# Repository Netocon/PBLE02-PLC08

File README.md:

# PBLE02-PLC08
Repositório da placa 8 (2026.1) da matéria PBLE02 da Universidade Federal de Itajubá.

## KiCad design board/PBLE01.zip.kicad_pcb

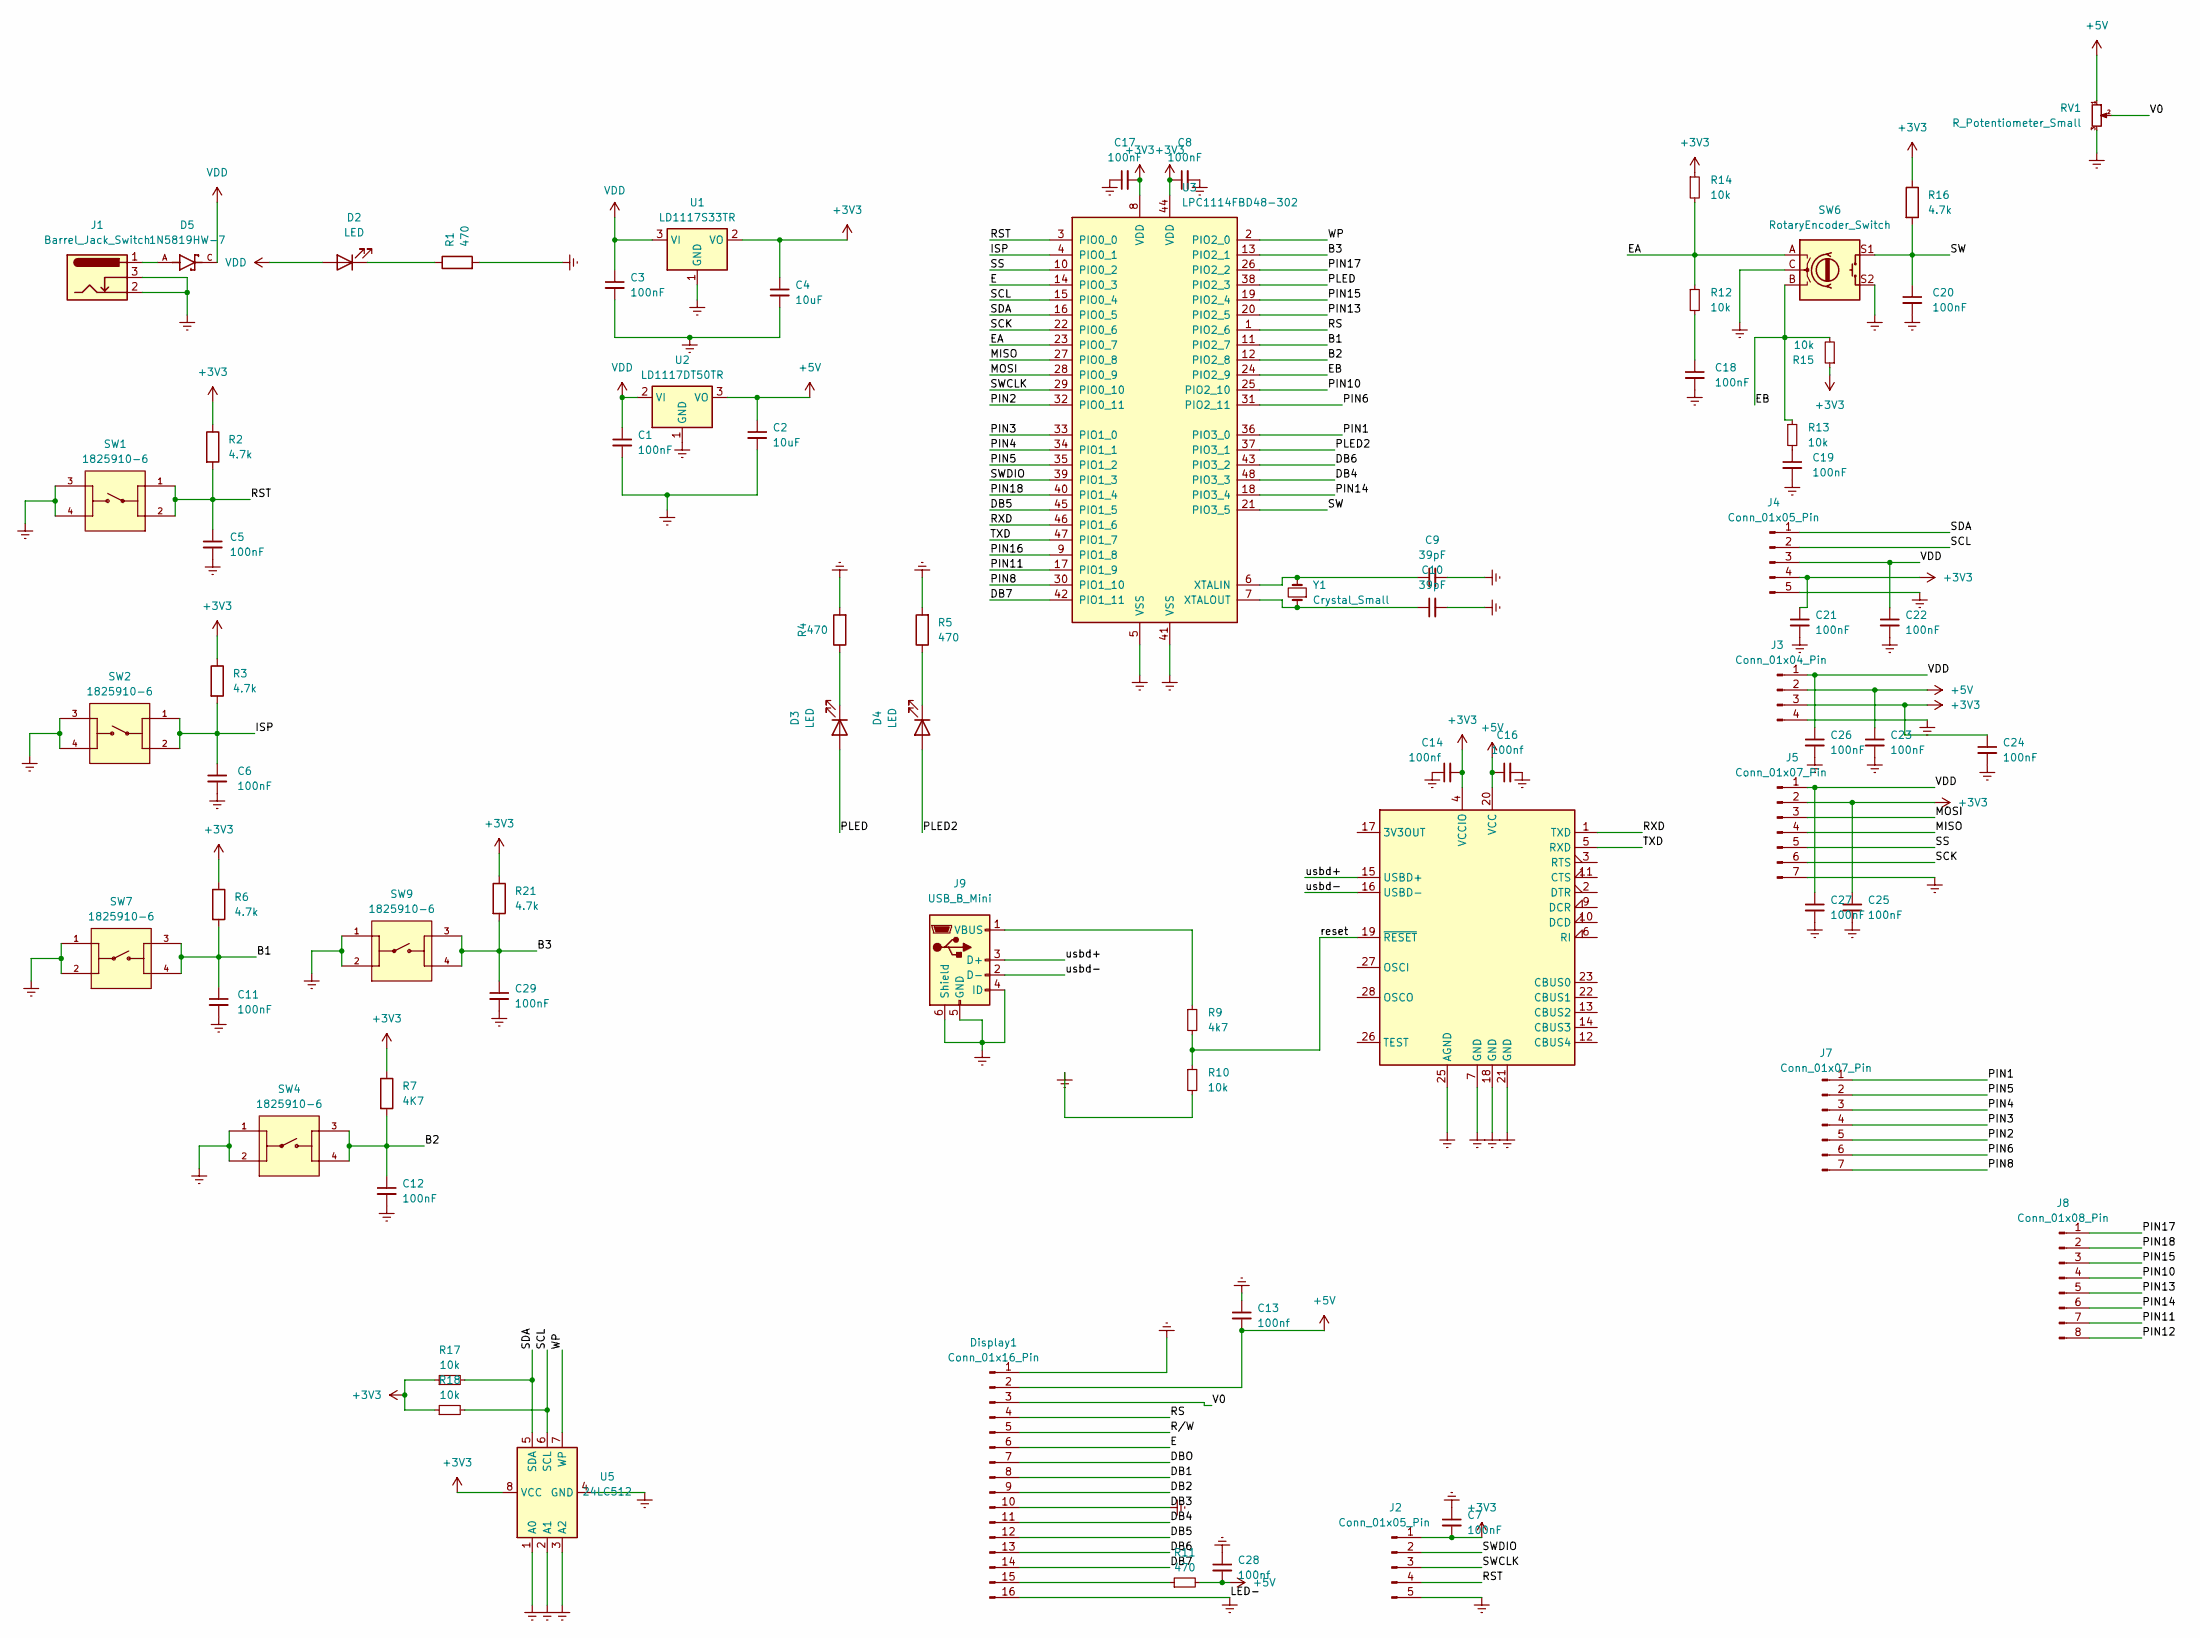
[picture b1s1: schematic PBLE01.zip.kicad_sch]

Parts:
C1, C3, C5, C6, C7, C8, C11, C12, C17, C18, C19, C20, C21, C22, C23, C24, C25, C26, C27, C29: 100nF; C_0805_2012Metric
C2, C4: 10uF; C_0805_2012Metric
C9, C10: 39pF; C_0805_2012Metric
C13, C14, C16, C28: 100nf; C_0805_2012Metric
D2, D3, D4: LED; D_1206_3216Metric
D5: 1N5819HW-7; Diode-1N5819HW7; PARTREV 18-2
Display1: Conn_01x16_Pin; PinHeader_1x16_P2.54mm_Vertical
J1: Barrel_Jack_Switch; CUI_PJ-002A
J2, J4: Conn_01x05_Pin; PinHeader_1x05_P2.54mm_Vertical
J3: Conn_01x04_Pin; PinHeader_1x04_P2.54mm_Vertical
J5, J7: Conn_01x07_Pin; PinHeader_1x07_P2.54mm_Vertical
J8: Conn_01x08_Pin; PinHeader_1x08_P2.54mm_Vertical
J9: USB_B_Mini; USB_Mini-B_Lumberg_2486_01_Horizontal
R1, R4, R5, R11: 470; R_0805_2012Metric
R2, R3, R6, R16, R21: 4.7k; R_0805_2012Metric
R7: 4K7; R_0805_2012Metric
R9: 4k7; R_0805_2012Metric
R10, R12, R13, R14, R15, R17, R18: 10k; R_0805_2012Metric
RV1: R_Potentiometer_Small; Potentiometer_Bourns_3314G_Vertical
SW1, SW2, SW4, SW7, SW9: 1825910-6; SW_1825910-6-4; PARTREV C10
SW6: RotaryEncoder_Switch; RotaryEncoder_Bourns_Vertical_PEC12R-3xxxF-Sxxxx
U1: LD1117S33TR; SOT-223-3_TabPin2
U2: LD1117DT50TR; DPAKSTM
U3: LPC1114FBD48-302; LQFP-48_7x7mm_P0.5mm
U4: FT232RL; SSOP-28_5.3x10.2mm_P0.65mm
U5: 24LC512; E2PROM SOIC127P794X203 8N
Y1: Crystal_Small; Crystal_HC49-4H_Vertical

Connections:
+3V3: C4.1, C7.2, C8.1, C14.2, C17.2, C21.1, C24.1, C25.1, J2.1, J3.3, J4.4, J5.2, R2.1, R3.1, R6.1, R7.1, R14.1, R15.1, R16.1, R17.1, R18.1, R21.1, U1.2 (VO), U3.8 (VDD), U3.44 (VDD), U4.4 (VCCIO), U5.8 (VCC)
+5V: C2.1, C13.2, C16.1, C23.1, C28.2, Display1.2, J3.2, R11.2, RV1.1, U2.3 (VO), U4.20 (VCC); also elsewhere on the board
/B1: C11.1, R6.2, SW7.3, SW7.4, U3.11 (PIO2_7)
/B2: C12.1, R7.2, SW4.3, SW4.4, U3.12 (PIO2_8)
/B3: C29.1, R21.2, SW9.3, SW9.4, U3.13 (PIO2_1)
/DB1: Display1.8
/DB2: Display1.9
/DB4: Display1.11, U3.48 (PIO3_3)
/DB5: Display1.12, U3.45 (PIO1_5)
/DB6: Display1.13, U3.43 (PIO3_2)
/DB7: Display1.14, U3.42 (PIO1_11)
/DBO: Display1.7
/E: Display1.6, U3.14 (PIO0_3)
/EA: R12.1, R14.2, SW6.A, U3.23 (PIO0_7)
/EB: R13.1, R15.2, SW6.B, U3.24 (PIO2_9)
/ISP: C6.1, R3.2, SW2.1, SW2.2, U3.4 (PIO0_1)
/MISO: J5.4, U3.27 (PIO0_8)
/MOSI: J5.3, U3.28 (PIO0_9)
/PIN1: J7.1, U3.36 (PIO3_0)
/PIN2: J7.5, U3.32 (PIO0_11)
/PIN3: J7.4, U3.33 (PIO1_0)
/PIN4: J7.3, U3.34 (PIO1_1)
/PIN5: J7.2, U3.35 (PIO1_2)
/PIN6: J7.6, U3.31 (PIO2_11)
/PIN8: J7.7, U3.30 (PIO1_10)
/PIN10: J8.4, U3.25 (PIO2_10)
/PIN11: J8.7, U3.17 (PIO1_9)
/PIN12: J8.8
/PIN13: J8.5, U3.20 (PIO2_5)
/PIN14: J8.6, U3.18 (PIO3_4)
/PIN15: J8.3, U3.19 (PIO2_4)
/PIN16: U3.9 (PIO1_8)
/PIN17: J8.1, U3.26 (PIO2_2)
/PIN18: J8.2, U3.40 (PIO1_4)
/PLED: D3.2 (A), U3.38 (PIO2_3)
/PLED2: D4.2 (A), U3.37 (PIO3_1)
/RS: Display1.4, U3.1 (PIO2_6)
/RST: C5.1, J2.4, R2.2, SW1.1, SW1.2, U3.3 (PIO0_0)
/RXD: U3.46 (PIO1_6), U4.1 (TXD)
/R/W: Display1.5
/SCK: J5.6, U3.22 (PIO0_6)
/SCL: J4.2, R18.2, U3.15 (PIO0_4), U5.6 (SCL)
/SDA: J4.1, R17.2, U3.16 (PIO0_5), U5.5 (SDA)
/SS: J5.5, U3.10 (PIO0_2)
/SW: C20.1, R16.2, SW6.S1, U3.21 (PIO3_5)
/SWCLK: J2.3, U3.29 (PIO0_10)
/SWDIO: J2.2, U3.39 (PIO1_3)
/TXD: U3.47 (PIO1_7), U4.5 (RXD)
/V0: Display1.3, RV1.2
/WP: U3.2 (PIO2_0), U5.7 (WP)
/reset: R9.2, R10.1, U4.19 (~RESET)
/usbd+: J9.3 (D+), U4.15 (USBD+)
/usbd-: J9.2 (D-), U4.16 (USBD-)
Earth: C1.2, C2.2, C3.2, C4.2, C5.2, C6.2, C7.1, C8.2, C9.2, C10.2, C11.2, C12.2, C13.1, C14.1, C16.2, C17.1, C18.2, C19.2, C20.2, C21.2, C22.2, C23.2, C24.2, C25.2, C26.2, C27.2, C28.1, C29.2, Display1.1, Display1.10, Display1.16, J1.2, J1.3, J2.5, J3.4, J4.5, J5.7, J9.4 (ID), J9.5 (GND), J9.6 (Shield), R1.2, R4.2, R5.2, R10.2, RV1.3, SW1.3, SW1.4, SW2.3, SW2.4, SW4.1, SW4.2, SW6.C, SW6.S2, SW7.1, SW7.2, SW9.1, SW9.2, U1.1 (GND), U2.1 (GND), U3.5 (VSS), U3.41 (VSS), U4.7 (GND), U4.18 (GND), U4.21 (GND), U4.25 (AGND), U5.1 (A0), U5.2 (A1), U5.3 (A2), U5.4 (GND); also elsewhere on the board
unnamed: C18.1, R12.2
unnamed: C19.1, R13.2
unnamed: D2.1 (K), R1.1
unnamed: D3.1 (K), R4.1
unnamed: D4.1 (K), R5.1
unnamed: D5.A, J1.1
unnamed: Display1.15, R11.1
unnamed: J9.1 (VBUS), R9.1
unnamed: C9.1, U3.6 (XTALIN), Y1.2
unnamed: C10.1, U3.7 (XTALOUT), Y1.1
VDD: C1.1, C3.1, C22.1, C26.1, C27.1, D2.2 (A), D5.C, J3.1, J4.3, J5.1, U1.3 (VI), U2.2 (VI)

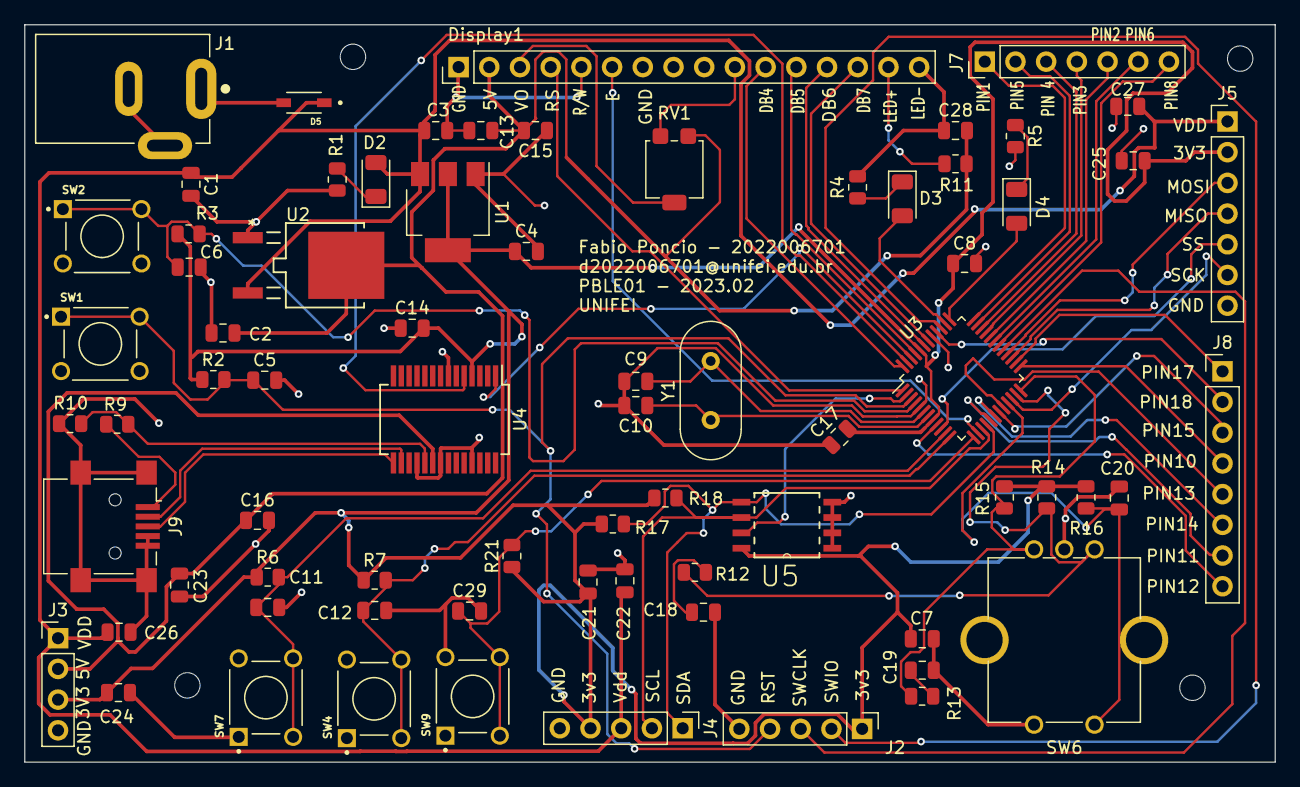
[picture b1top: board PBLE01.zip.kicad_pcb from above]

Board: 2 copper layers, 103.5 x 61.0 mm, 73 parts (0 on the bottom side), 59 nets.

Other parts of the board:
C15: 100nf; C_0805_2012Metric

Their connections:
+5V: C15.2; also elsewhere on the board
Earth: C15.1; also elsewhere on the board
